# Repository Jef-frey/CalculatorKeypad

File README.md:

# CalculatorKeypad(WIP)
This project is still a work in progress, the goal is to create a device that can switch between calculator and computer keypad function with the flip of a switch 

# Requirements
## Hardware
1x OLIMEX ESP32-S3-DevKit-LiPo development board<br />
1x OLED display<br />
1x battery<br />
1x USB cables<br />
2x slide switch<br />
Switches that fit your application (17 for my project)<br />

## Software
Arduino IDE<br />
U8G2 library<br />
 
# Connection
Pins used and connected for the OLED display are written on the [`oled.cpp`](software/oled.cpp) file and the changable pins are stored on the [`oled.h`](software/oled.h) file, they are for the SPI 256x64 OLED Display with Screen Driver SH1122 used in my project, if a different display is used, a different u8g2 constructor may be used with different connections. And the SPI pins for the OLED display may also need to be changed if a different development board is used.<br />
Pins used for the keypad connections are written on the [`keyboard.h`](software/keyboard.h) file inside the variables KEY_PINS and MODE_SEL_PIN, different pins on the board can be used if available.<br />

# Battery Voltage
The original code from Olimex for battery voltage reading reads the voltage level, to display the voltage as a percentage, a script called [`plotVoltage.ino`](software/battery_level/plotVoltage.ino) is created. It measures the voltage and the time of the measurement and prints the measured values upon request. Part of this code is modified from https://dronebotworkshop.com/esp32-non-volatile-storage/ <br />
To use this script:
1. upload the script with the necessary include files at the same directory
2. charge the device with the battery until it is full
3. unplug the device and press '1' on the keypad
4. wait until the display no longer lights up (run out of power)
5. prepare a program that can accept UART signal and turn the data into a csv file (I used Tera Term for this step)
6. plug in the device at the UART port and press '2' on the keypad
7. plot the csv file

For instance this is the plot of the 420mAh Lipo battery I use

# Reference
Software related to battery sensing is from OLIMEX, it's license GPL3 is included in this repository <br />
https://github.com/OLIMEX/ESP32-S3-DevKit-LiPo/blob/main/SOFTWARE/Arduino/ESP32-S3-DevKit-Lipo-bat-sense/ESP32-S3-DevKit-Lipo-bat-sense.ino <br />
Software related to storing data in esp32 and outputing data from esp32 is from https://dronebotworkshop.com/esp32-non-volatile-storage/

# Future plans
Add a case for the device<br />

Use ESP32S3 module instead of a development board, as the development board uses voltage dividers that contribute to leakage current<br />
Implement Bluetooth feature for the keypad<br />

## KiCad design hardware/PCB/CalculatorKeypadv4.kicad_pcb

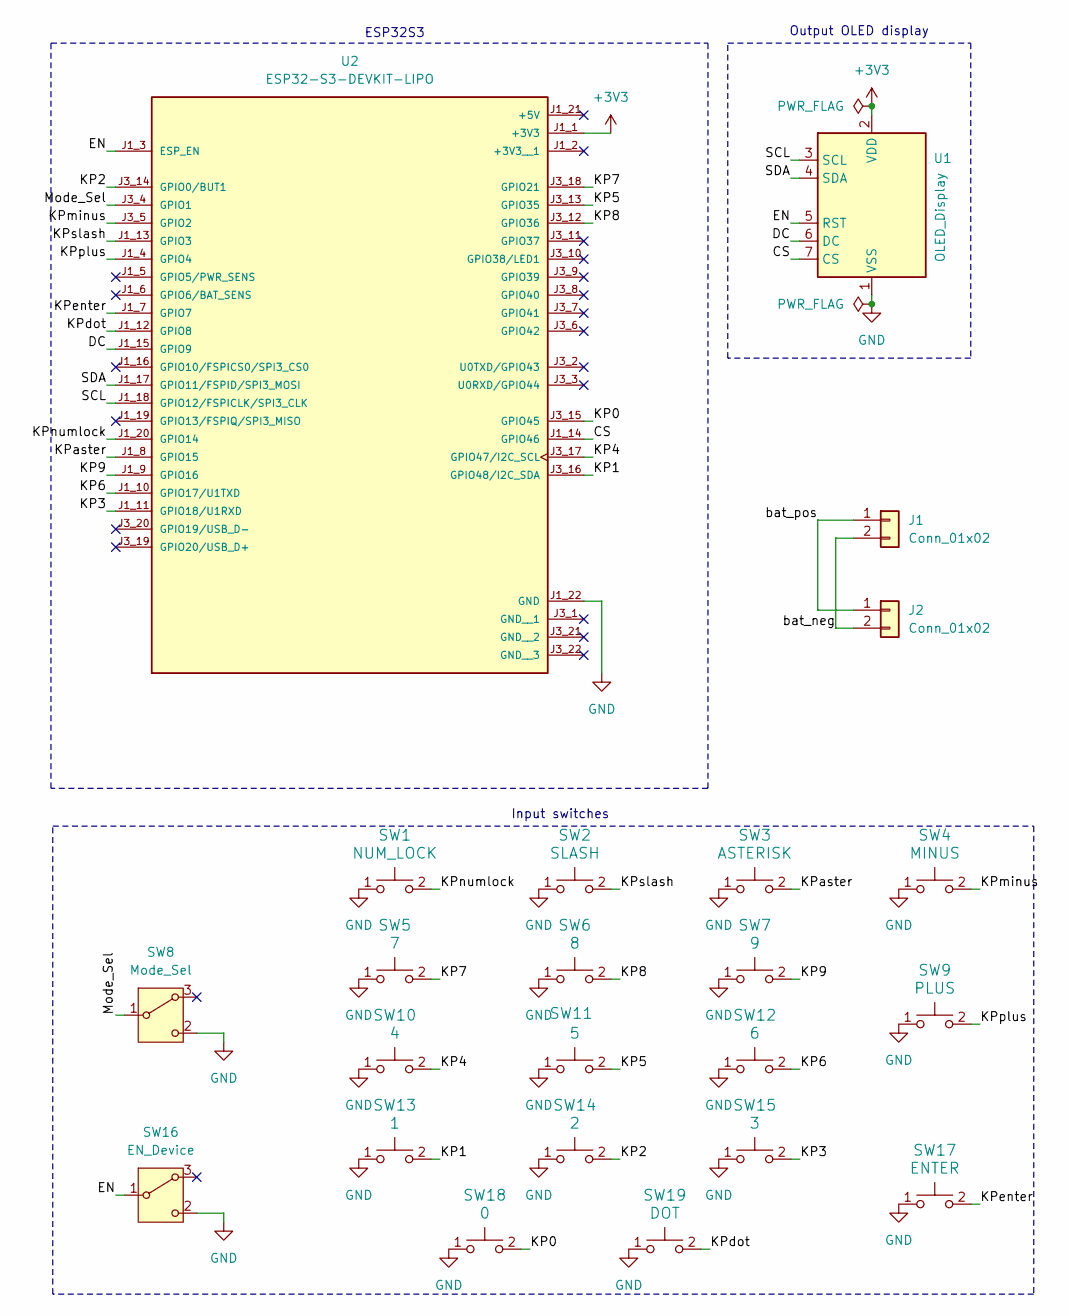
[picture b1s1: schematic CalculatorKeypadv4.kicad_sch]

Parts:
J1: Conn_01x02; JST_PH_B2B-PH-K_1x02_P2.00mm_Vertical
J2: Conn_01x02; JST_PH_S2B-PH-K_1x02_P2.00mm_Horizontal
SW1: NUM_LOCK; SW_Cherry_MX_1.00u_Plate_w_3Dmodel
SW2: SLASH; SW_Cherry_MX_1.00u_Plate_w_3Dmodel
SW3: ASTERISK; SW_Cherry_MX_1.00u_Plate_w_3Dmodel
SW4: MINUS; SW_Cherry_MX_1.00u_Plate_w_3Dmodel
SW5: 7; SW_Cherry_MX_1.00u_Plate_w_3Dmodel
SW6: 8; SW_Cherry_MX_1.00u_Plate_w_3Dmodel
SW7: 9; SW_Cherry_MX_1.00u_Plate_w_3Dmodel
SW8: Mode_Sel; slide_switch
SW9: PLUS; SW_Cherry_MX_2.00u_Vertical_Plate
SW10: 4; SW_Cherry_MX_1.00u_Plate_w_3Dmodel
SW11: 5; SW_Cherry_MX_1.00u_Plate_w_3Dmodel
SW12: 6; SW_Cherry_MX_1.00u_Plate_w_3Dmodel
SW13: 1; SW_Cherry_MX_1.00u_Plate_w_3Dmodel
SW14: 2; SW_Cherry_MX_1.00u_Plate_w_3Dmodel
SW15: 3; SW_Cherry_MX_1.00u_Plate_w_3Dmodel
SW16: EN_Device; slide_switch
SW17: ENTER; SW_Cherry_MX_2.00u_Vertical_Plate
SW18: 0; SW_Cherry_MX_2.00u_Plate
SW19: DOT; SW_Cherry_MX_1.00u_Plate_w_3Dmodel
U1: OLED_Display; OLED_display
U2: ESP32-S3-DEVKIT-LIPO; XCVR_ESP32-S3-DEVKIT-LIPO; PARTREV B

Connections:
+3V3: U1.2 (VDD), U2.J1_1 (+3V3)
/CS: U1.7 (CS), U2.J1_14 (GPIO46)
/DC: U1.6 (DC), U2.J1_15 (GPIO9)
/EN: SW16.1 (B), U1.5 (RST), U2.J1_3 (ESP_EN)
/KP0: SW18.2, U2.J3_15 (GPIO45)
/KP1: SW13.2, U2.J3_16 (GPIO48/I2C_SDA)
/KP2: SW14.2, U2.J3_14 (GPIO0/BUT1)
/KP3: SW15.2, U2.J1_11 (GPIO18/U1RXD)
/KP4: SW10.2, U2.J3_17 (GPIO47/I2C_SCL)
/KP5: SW11.2, U2.J3_13 (GPIO35)
/KP6: SW12.2, U2.J1_10 (GPIO17/U1TXD)
/KP7: SW5.2, U2.J3_18 (GPIO21)
/KP8: SW6.2, U2.J3_12 (GPIO36)
/KP9: SW7.2, U2.J1_9 (GPIO16)
/KPaster: SW3.2, U2.J1_8 (GPIO15)
/KPdot: SW19.2, U2.J1_12 (GPIO8)
/KPenter: SW17.2, U2.J1_7 (GPIO7)
/KPminus: SW4.2, U2.J3_5 (GPIO2)
/KPnumlock: SW1.2, U2.J1_20 (GPIO14)
/KPplus: SW9.2, U2.J1_4 (GPIO4)
/KPslash: SW2.2, U2.J1_13 (GPIO3)
/Mode_Sel: SW8.1 (B), U2.J3_4 (GPIO1)
/SCL: U1.3 (SCL), U2.J1_18 (GPIO12/FSPICLK/SPI3_CLK)
/SDA: U1.4 (SDA), U2.J1_17 (GPIO11/FSPID/SPI3_MOSI)
/bat_neg: J1.2, J2.2
/bat_pos: J1.1, J2.1
GND: SW1.1, SW2.1, SW3.1, SW4.1, SW5.1, SW6.1, SW7.1, SW8.2 (C), SW9.1, SW10.1, SW11.1, SW12.1, SW13.1, SW14.1, SW15.1, SW16.2 (C), SW17.1, SW18.1, SW19.1, U1.1 (VSS), U2.J1_22 (GND)

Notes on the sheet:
ESP32S3
Input switches
Output OLED display

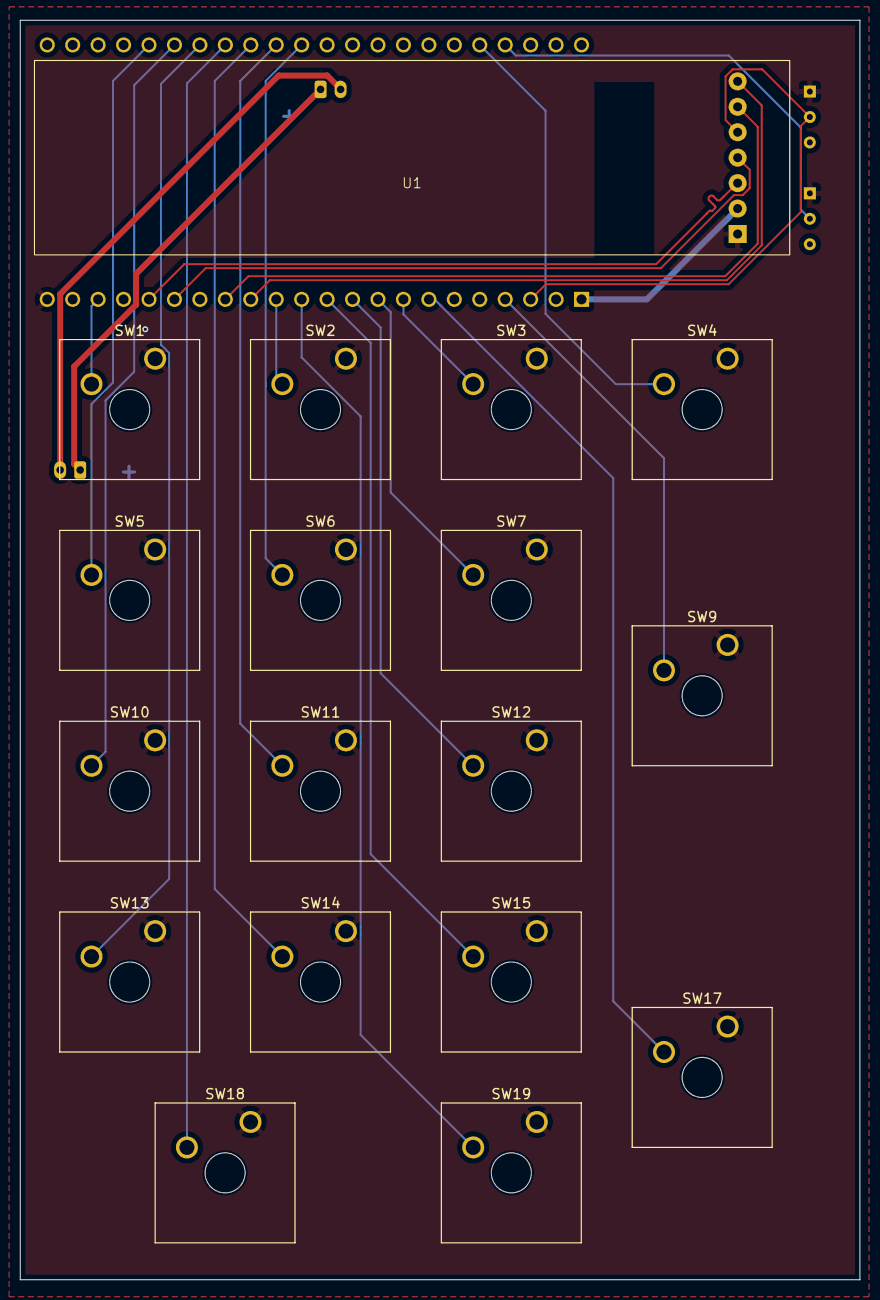
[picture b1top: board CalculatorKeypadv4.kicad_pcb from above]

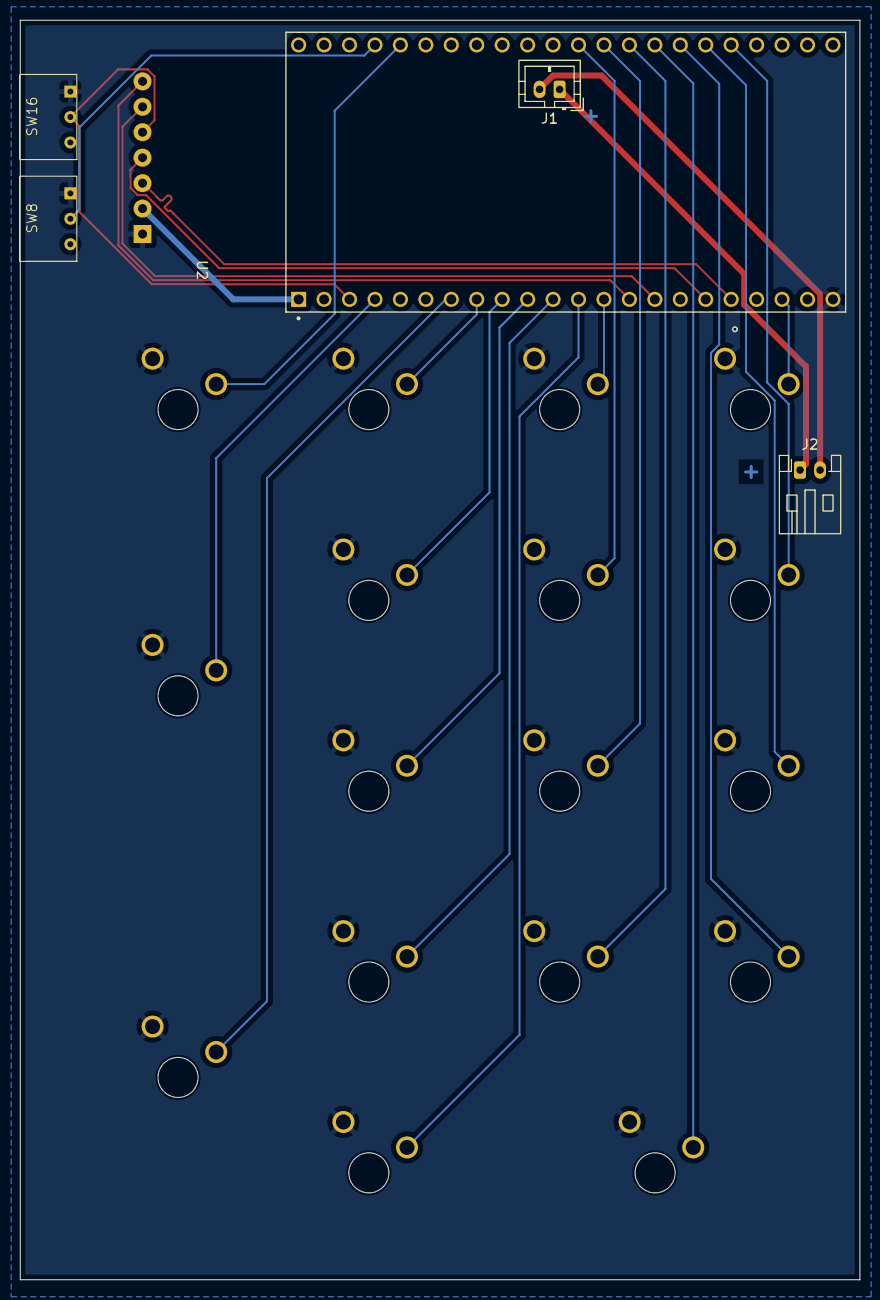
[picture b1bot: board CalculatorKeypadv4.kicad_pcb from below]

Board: 2 copper layers, 83.8 x 125.7 mm, 23 parts (5 on the bottom side), 27 nets.

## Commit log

2025-06-25 Add files via upload
    Adding version 1 of this project
2025-06-26 This version test for OLED screen only, output HELLO_WORLD and other characters to screen upon loading
2025-06-27 Edited the input module, any switch pressed will be displayed onto the OLED display
2025-06-29 Finished the calculator display function to properly display the calculation action
2025-06-30 Updated the computation function, this stage of calculator is a functioning calculator
2025-07-03 Add files via upload
    Sample code to add the keypad feature
2025-07-03 Try to merge calculator and keypad feature together
2025-07-03 Finished the most basic calculator and keypad integration
2025-07-03 Add files via upload
    Add an image of the device prototype
2025-07-03 Update README.md
    Added hyperlinks for better navigation
2025-07-07 change mode switching method and changed pin locations for PCB layout
2025-07-25 Create sample
    create an image folder
2025-07-25 Rename CalculatorKeypad.png to image/CalculatorKeypad.png
2025-07-25 Rename CalculatorKeypad_prototype.jpg to image/CalculatorKeypad_prototype.jpg
2025-07-25 Create temp
2025-07-25 Rename CalculatorKeypad.ino to software/CalculatorKeypad.ino
2025-07-25 move all the code to a different folder
2025-07-25 move the files to 'software' folder
2026-04-28 updated the software for switching to OLIMEX development board
2026-04-28 Added the PCB files and documentation for OLIMEX dev board
2026-04-28 Old images no longer relevant after switching to dev board
2026-04-29 Update LinkedList.cpp
    Solved a bug that crash the device when computing the formula a second time
2026-05-01 Update README.md
    Updated some images
2026-05-01 Removed the files from zip file
2026-05-03 Added a script to store the voltage level with respect to time, and then plot it later. the goal is to plot it to calculate battery capacity at different voltage level. Part of the code is taken from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
2026-05-03 Original the voltage reading is the voltage level at the moment the read function is called, but now the voltage level displayed on the screen will be the average of past voltage reading. The voltage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
2026-05-03 Added the dxf file for the case that will be laser-cut
2026-05-03 Update README.md
    Update with instruction and explanation of new features
